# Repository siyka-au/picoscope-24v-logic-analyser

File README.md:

# Picoscope 24V logic analyser
An adapter developed by user 'bennog' on PicoTech Test & Measurement forum.
https://www.picotech.com/support/topic41135.html

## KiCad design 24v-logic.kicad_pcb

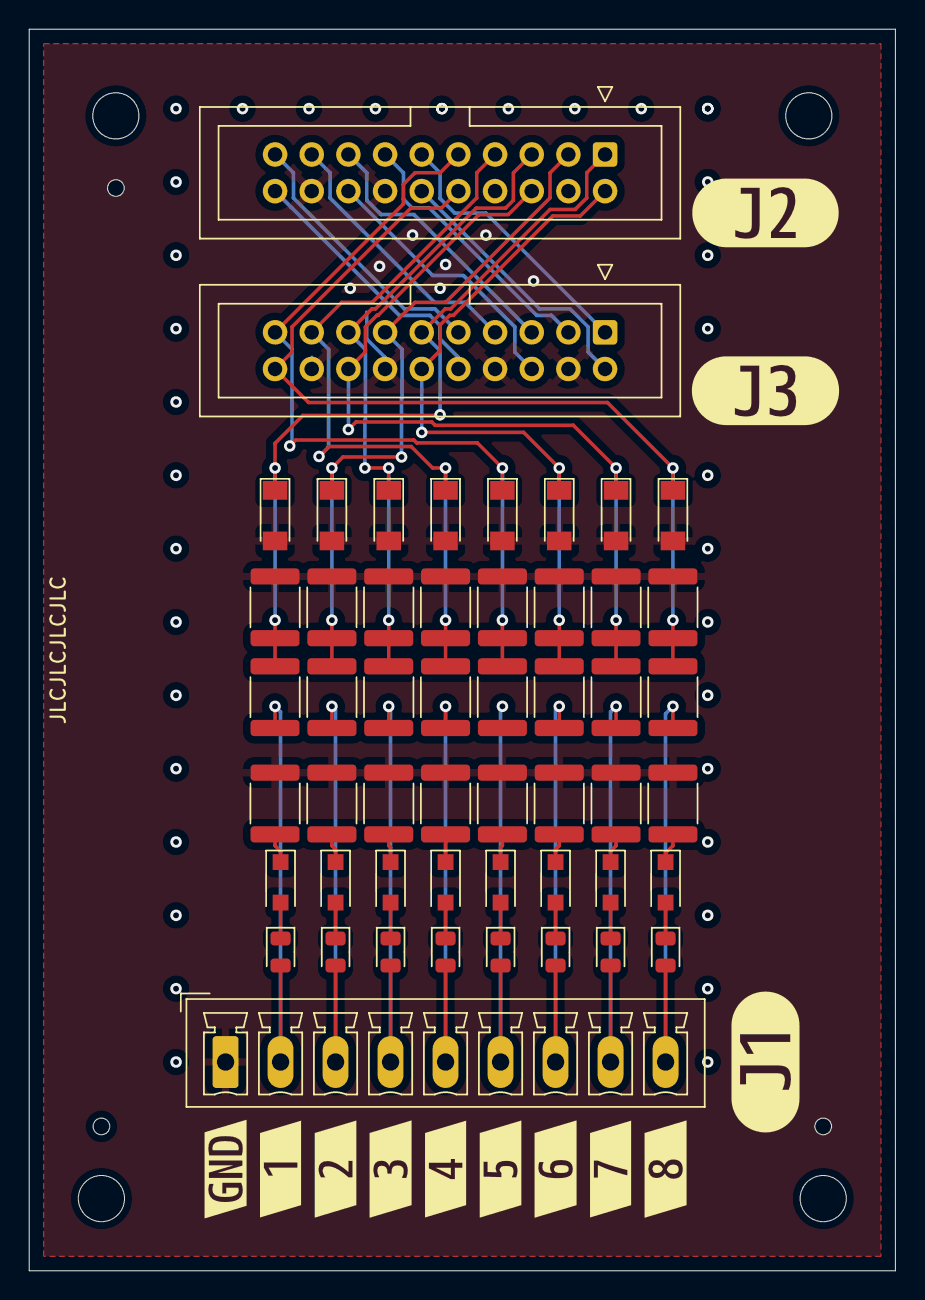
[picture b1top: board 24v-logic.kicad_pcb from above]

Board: 2 copper layers, 60.0 x 86.0 mm, 67 parts (0 on the bottom side), 41 nets.

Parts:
D1, D3, D5, D7, D9, D12, D13, D15: D; D_SOD-123F
D2, D4, D6, D8, D10, D11, D14, D16: R; D_0805_2012Metric
D17, D18, D19, D20, D21, D22, D23, D24: 5,6V; D_MiniMELF
H1, H2, H3, H4: MountingHole; MountingHole_3.2mm_M3
J1: Screw_Terminal_01x09; PhoenixContact_MCV_1,5_9-G-3.81_1x09_P3.81mm_Vertical
J2, J3: Conn_02x10_Odd_Even; IDC-Header_2x10_P2.54mm_Vertical
R1, R2, R5, R10, R14, R16, R19, R22: 1k; R_1812_4532Metric
R3, R4, R6, R7, R8, R9, R11, R12, R13, R15, R17, R18, R20, R21, R23, R24: 3.9k; R_1812_4532Metric
kibuzzard-62FC7CD0: G***; kibuzzard-62FC7CD0
kibuzzard-62FC7D6D: G***; kibuzzard-62FC7D6D
kibuzzard-62FC7D50: G***; kibuzzard-62FC7D50
kibuzzard-62FC79A9: G***; kibuzzard-62FC79A9
kibuzzard-62FC79AF: G***; kibuzzard-62FC79AF
kibuzzard-62FC79B6: G***; kibuzzard-62FC79B6
kibuzzard-62FC79BD: G***; kibuzzard-62FC79BD
kibuzzard-62FC794D: G***; kibuzzard-62FC794D
kibuzzard-62FC799A: G***; kibuzzard-62FC799A
kibuzzard-62FC7920: G***; kibuzzard-62FC7920
kibuzzard-62FC7940: G***; kibuzzard-62FC7940
kibuzzard-62FC7992: G***; kibuzzard-62FC7992

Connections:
D0: D21.1 (K), J2.1, J3.11, R13.1, R14.2
D1: D17.1 (K), J2.3, J3.13, R10.2, R11.1
D2: D18.1 (K), J2.5, J3.15, R1.2, R8.1
D3: D19.1 (K), J2.7, J3.17, R5.2, R6.1
D4: D20.1 (K), J2.9, J3.19, R2.2, R3.1
D5: D23.1 (K), J2.2, J3.12, R21.1, R22.2
D6: D24.1 (K), J2.6, J3.16, R16.2, R24.1
D7: D22.1 (K), J2.10, J3.20, R18.1, R19.2
D8: J2.11, J3.1
D9: J2.13, J3.3
D10: J2.15, J3.5
D11: J2.17, J3.7
D12: J2.19, J3.9
D13: J2.12, J3.2
D14: J2.16, J3.6
D15: J2.20, J3.10
GND: D17.2 (A), D18.2 (A), D19.2 (A), D20.2 (A), D21.2 (A), D22.2 (A), D23.2 (A), D24.2 (A), J1.1, J2.4, J2.8, J2.14, J2.18, J3.4, J3.8, J3.14, J3.18, R1.1, R2.1, R4.1, R5.1, R7.1, R9.1, R10.1, R12.1, R14.1, R15.1, R16.1, R17.1, R19.1, R20.1, R22.1, R23.1
I24-0: D10.2 (A), J1.2, R13.2
I24-1: D2.2 (A), J1.3, R11.2
I24-2: D8.2 (A), J1.4, R8.2
I24-3: D6.2 (A), J1.5, R6.2
I24-4: D4.2 (A), J1.6, R3.2
I24-5: D11.2 (A), J1.7, R21.2
I24-6: D14.2 (A), J1.8, R24.2
I24-7: D16.2 (A), J1.9, R18.2
unnamed: D9.2 (A), D10.1 (K)
unnamed: D9.1 (K), R12.2
unnamed: D13.2 (A), D16.1 (K)
unnamed: D13.1 (K), R17.2
unnamed: D1.2 (A), D2.1 (K)
unnamed: D1.1 (K), R15.2
unnamed: D7.2 (A), D8.1 (K)
unnamed: D7.1 (K), R9.2
unnamed: D5.2 (A), D6.1 (K)
unnamed: D5.1 (K), R7.2
unnamed: D3.2 (A), D4.1 (K)
unnamed: D3.1 (K), R4.2
unnamed: D11.1 (K), D12.2 (A)
unnamed: D12.1 (K), R20.2
unnamed: D14.1 (K), D15.2 (A)
unnamed: D15.1 (K), R23.2

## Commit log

2022-08-17 Changes for missing components and migrating to KiCAD 6
